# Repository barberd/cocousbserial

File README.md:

# CoCo USB Serial Cartridge

## Description

This board is a cartridge for the Tandy Radio Shack TRS-80 Color Computer (CoCo), an 8 bit computer produced between 1980 and 1991. It provides an interface that allows for a serial connection over a USB connection to a host computer (typically a modern PC).

Schematic is available [here](kicad/6551usb.pdf).

## Source and License

Design maintained at [https://github.com/barberd/cocousbserial](https://github.com/barberd/cocousbserial). [Kicad](https://www.kicad.org/) and [Freerouting](https://github.com/freerouting/freerouting/) were used to design the board.

The design is copyright 2023 by Don Barber. The design is open source, distributed via the GNU GPL version 3 license. Please see the COPYING file for details.

## Interface

The board replicates the interface for original CoCo devices based on the 6551 ACIA chip, such as the Deluxe RS-232 Pak and the Direct Connect Modem Pak. Most of the behavior of the 6551 is duplicated, including the status, command, and control registers. One exception is a lack of hardware loopback support; another is the reset values of the registers (see next paragraph). Interrupts are supported, including those triggered by an empty transmit buffer, received data, or a change in connection status. For the latter, changes in USB connection status are used instead of the DCD and DSR lines used in a rs-232 serial connection.

The registers are not set in the same way as the 6551 upon reset or power-on. As most software does its own initialization of the registers when starting anyway, the lack of this functionality has little practical effect. However, it is possible that the card receiving USB data before the software has set up (or disabled) interrupt handling might lead to an unhandled interrupt, which could potentially lock up the system. The easiest workaround is to just not send data from the USB host until after the CoCo software has initialized the card.

Settings in the command or control registers that do not apply to a USB connection or are performed by the USB protocol (such as baud rate, parity, bitrate, and stop bit settings) are ignored. Bitflags in the status register that do not apply or are abstracted away by the USB module (such as parity, framing, or overrun errors) are tied to 0.

## Why duplicate a legacy hardware interface?

Duplicating the behavior of the 6551 in this way allows one to use original CoCo software written for the Deluxe RS-232 Pak or Direct Connect Modem Pak without modification. Additionally, the use of standard TTL chips (when combined with the USB module) allows one to build the board at home without the need for specialized chips such as a programmed microcontroller.

## USB Capability

The USB module used is the DLP-USB245R. [Here is its manufacturer's page](https://www.dlpdesign.com/usb/usb245r.php). The module can be purchased directly from the manufacturer or from electronics supply houses such as Jameco and Mouser. This module abstracts away much of the heavy lifting needed for USB communications. This module acts as a client device, communicating with a USB host, typically a modern PC. It does NOT support host mode, meaning it can not be used as a host for other peripherals such as keyboard and mice; it only provides a client serial connection. The DLP-USB1232H module is also pin-compatible with the board, though one will need to configure that module into DLP-USB245R (FIFO) mode using the manufacturer's configuration software.

## IO Address

The 6 dip switches (SW1) set the IO addresses for the board. These correspond to address lines A2 through A7. The four addresses used correspond to the board's (and the original 6551 chip's) four registers. Using the switches, one can configure the base address of the board to be any multiple of four within the range of FF00 through FFFC.

The Deluxe RS-232 Pak uses IO addresses FF68-FF6B while the Direct Connect Modem Pak uses FF6C-FF6F. Markings on the board make it straightforward to set the IO address of the board to clone either; this is the easiest way to use the board as one can then leverage existing software.

One may choose to use a different IO address range; this can be helpful if one has multiple paks that would otherwise conflict. If you use a non-standard range, software must be configured, patched, or updated to use the new IO address. Be mindful to review the CoCo's IO mapping and not choose an IO address used by another device, such as a keyboard, joystick, cassette, or disk controller.

## Power Draw

When hooked up to a bench power supply, the card drew 0.2 Amps.

Board version 1.09 added jumper J2 for the source of +5v power for the DLP-USB245R module, either the CoCo or the USB host. The module draws 15mA of power in normal operation. One should choose the USB host if one wants the module recognized by the host as soon as its plugged in, or wants the USB device to remain configured on the host even when the CoCo is power-cycled. One should choose the CoCo if one wants the device recognized only when the CoCo is powered on.

## ROM Socket

A socket for a ROM is also included in the board design. This is entirely optional, as most users today will instead choose to use a third-party communications software package loaded from another source such as disk, SDC, or DriveWire. However, one can add a ROM loaded with the Deluxe RS-232 Cartridge or Direct Connect Modem Cartridge software (or any other cartridge software) if one desires to replicate the original cartridge experience.

The ROM socket is wired for a 27128 EPROM. As the 27128 provides 16k of storage, the board presents this as 2 different banks of 8k each, selected via jumper J1. As such, when writing the EPROM, combine the images with each image aligned to an 8k boundary (eg, at 0 and 8k). If using a ROM IC other than the 27128, one will need to adjust the board design to match the chosen IC. Some other ROM ICs are pin-compatible and will work fine with the existing design.

### Starting the ROM software

Please note that since the cartridge interrupt line is used for serial communications interrupts and not for the cartridge start interrupt, this cartridge does not auto-start. As such, one will need to start the ROM software manually with an "EXEC &HC000" or "EXEC 49152" statement, just as described in the [Deluxe RS-232 Pak](https://colorcomputerarchive.com/repo/Documents/Manuals/Hardware/Deluxe%20RS-232%20Operation%20Manual%20%28Tandy%29.pdf) and [Direct Connect Modem Pak](https://colorcomputerarchive.com/repo/Documents/Manuals/Hardware/Direct%20Connect%20Modem%20Pak%20%28Tandy%29.pdf) manuals.

Note the Color Computer 3 maps the cartridge memory differently than the CoCo 1 and CoCo 2; use "EXEC 57360" or "EXEC &HE010" instead.

## Physical case

The board is sized to fit into an original large CoCo pak, such as the Deluxe RS-232 Pak or a Disk Controller Pak. One can also 3D print a case such as [this  one found on thingiverse](https://www.thingiverse.com/thing:4829413).

## How to order for fabrication

Download 6551usb-fabrication.zip, then upload it to your PCB manufacturer of choice when asked to provide Gerber files. Usually this is found under a 'Quote' option on the website. Search "pcb manufacturing" on any major search engine to get several manufacturers.

Some may have ordered boards and have extra available. Reach out to don &#x40; dgb3.net to explore this.

## Errata

If you have version 1.04 or 1.05 of the board, there a 'bug' in the reset circuit for the change-in-plugged-in-status interrupt in that the interrupt is not cleared when the status register is read. I'm not aware of any software that actually enables this in the first place, so one will likely never encouter the bug. But the fix is simple: bend up pin 6 on U12, and solder it to pin 6 on U5 with a bodge wire. R4 is also no longer needed. This is fixed in 1.06.

Boards prior to versions 1.08 were printed with 10nF capacitors, but .1uf (100nF) capacitors are bit more standard. Either work fine, they're just to smooth out ripples in the power to the ICs.

Board version 1.09 added jumper J2 for the USB module's source of +5v power; see 'Power Draw' section above.

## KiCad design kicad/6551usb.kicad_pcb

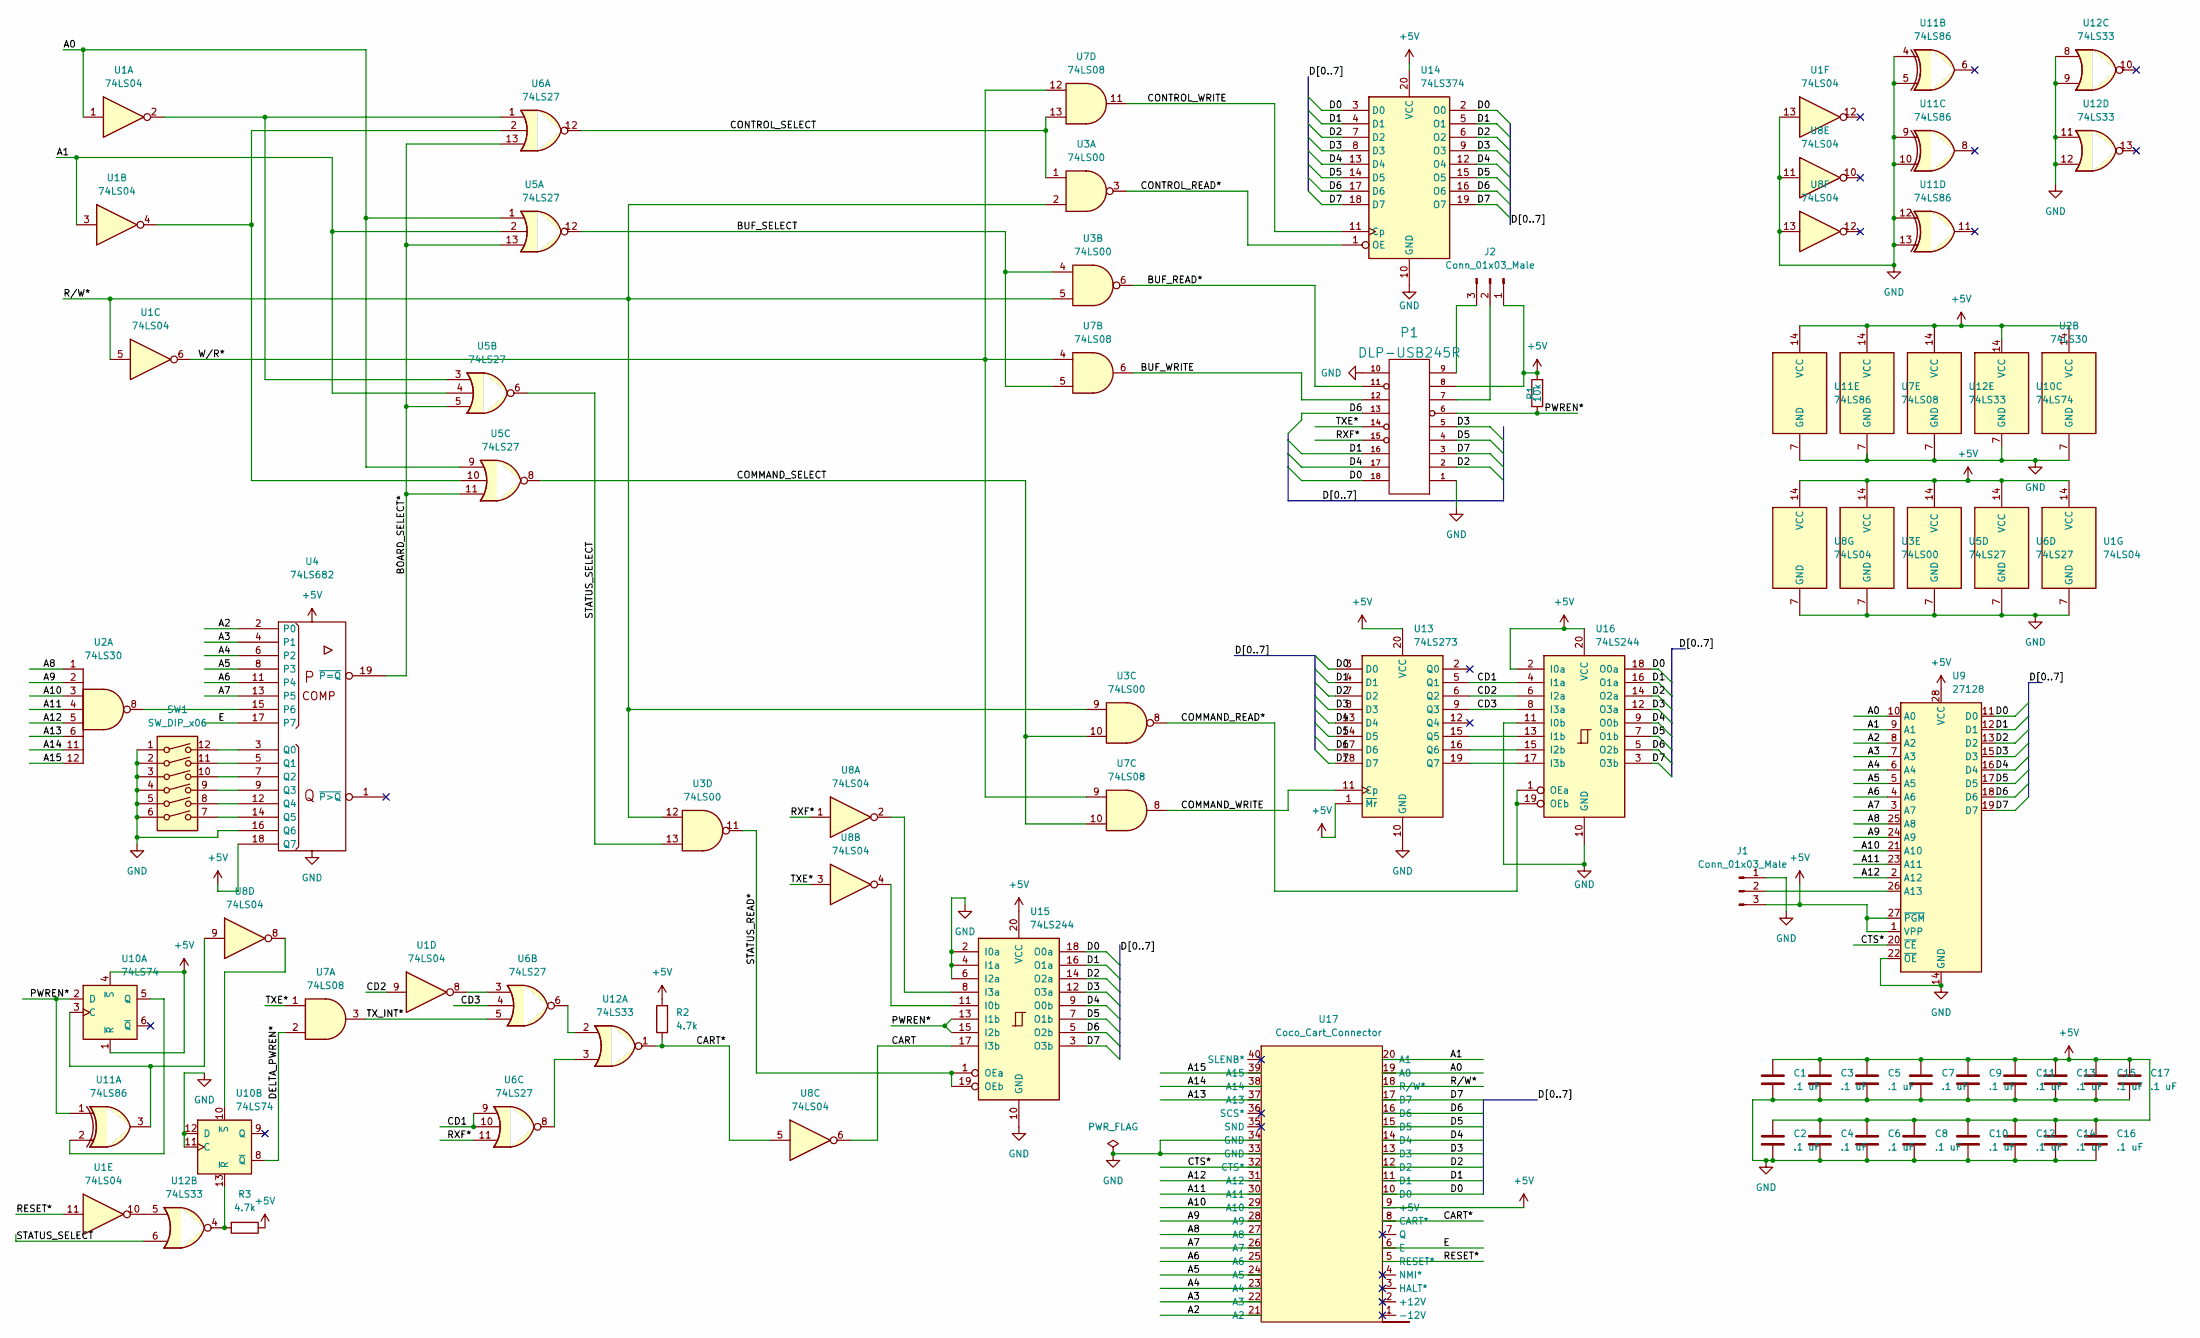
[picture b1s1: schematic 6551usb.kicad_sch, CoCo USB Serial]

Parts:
C1, C2, C3, C4, C5, C6, C7, C8, C9, C10, C11, C12, C13, C14, C15, C16, C17: .1 uF; C_Axial_L3.8mm_D2.6mm_P7.50mm_Horizontal
J1, J2: Conn_01x03_Male; PinHeader_1x03_P2.54mm_Vertical
P1: DLP-USB245R; DIP-18_W7.62mm_Socket
R1: 10k; R_Axial_DIN0207_L6.3mm_D2.5mm_P7.62mm_Horizontal
R2, R3: 4.7k; R_Axial_DIN0207_L6.3mm_D2.5mm_P7.62mm_Horizontal
SW1: SW_DIP_x06; SW_DIP_SPSTx06_Slide_9.78x17.42mm_W7.62mm_P2.54mm
U1, U8: 74LS04; DIP-14_W7.62mm
U2: 74LS30; DIP-14_W7.62mm
U3: 74LS00; DIP-14_W7.62mm
U4: 74LS682; DIP-20_W7.62mm
U5, U6: 74LS27; DIP-14_W7.62mm
U7: 74LS08; DIP-14_W7.62mm
U9: 27128; DIP-28_W15.24mm
U10: 74LS74; DIP-14_W7.62mm
U11: 74LS86; DIP-14_W7.62mm
U12: 74LS33; DIP-14_W7.62mm
U13: 74LS273; DIP-20_W7.62mm
U14: 74LS374; DIP-20_W7.62mm
U15, U16: 74LS244; DIP-20_W7.62mm
U17: Coco_Cart_Connector; Coco_Cart

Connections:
+5V: C1.1, C2.1, C3.1, C4.1, C5.1, C6.1, C7.1, C8.1, C9.1, C10.1, C11.1, C12.1, C13.1, C14.1, C15.1, C16.1, C17.1, J1.3, J2.1, P1.8 (EXTVCC), R1.2, R2.2, R3.1, U1.14 (VCC), U2.14 (VCC), U3.14 (VCC), U4.18 (Q7), U4.20 (Vcc), U5.14 (VCC), U6.14 (VCC), U7.14 (VCC), U8.14 (VCC), U9.1 (VPP), U9.27 (~PGM), U9.28 (VCC), U10.1 (~R), U10.4 (~S), U10.14 (VCC), U11.14 (VCC), U12.14 (VCC), U13.1 (~Mr), U13.20 (VCC), U14.20 (VCC), U15.20 (VCC), U16.2 (I0a), U16.20 (VCC), U17.9 (+5V)
/A0: U1.1, U5.1, U5.9, U9.10 (A0), U17.19 (A0)
/A1: U1.3, U5.2, U5.4, U9.9 (A1), U17.20 (A1)
/A2: U4.2 (P0), U9.8 (A2), U17.21 (A2)
/A3: U4.4 (P1), U9.7 (A3), U17.22 (A3)
/A4: U4.6 (P2), U9.6 (A4), U17.23 (A4)
/A5: U4.8 (P3), U9.5 (A5), U17.24 (A5)
/A6: U4.11 (P4), U9.4 (A6), U17.25 (A6)
/A7: U4.13 (P5), U9.3 (A7), U17.26 (A7)
/A8: U2.1, U9.25 (A8), U17.27 (A8)
/A9: U2.2, U9.24 (A9), U17.28 (A9)
/A10: U2.3, U9.21 (A10), U17.29 (A10)
/A11: U2.4, U9.23 (A11), U17.30 (A11)
/A12: U2.5, U9.2 (A12), U17.31 (A12)
/A13: U2.6, U17.37 (A13)
/A14: U2.11, U17.38 (A14)
/A15: U2.12, U17.39 (A15)
/BOARD_SELECT*: U4.19 (~P=Q), U5.5, U5.11, U5.13, U6.13
/BUF_READ*: P1.11 (RD*), U3.6
/BUF_SELECT: U3.4, U5.12, U7.5
/BUF_WRITE: P1.12 (WR), U7.6
/CART: U8.6, U15.17 (I3b)
/CART*: R2.1, U8.5, U12.1, U17.8 (CART*)
/CD1: U6.9, U6.10, U13.5 (Q1), U16.4 (I1a)
/CD2: U1.9, U13.6 (Q2), U16.6 (I2a)
/CD3: U6.4, U13.9 (Q3), U16.8 (I3a)
/COMMAND_READ*: U3.8, U16.1 (OEa), U16.19 (OEb)
/COMMAND_SELECT: U3.10, U5.8, U7.10
/COMMAND_WRITE: U7.8, U13.11 (Cp)
/CONTROL_READ*: U3.3, U14.1 (OE)
/CONTROL_SELECT: U3.1, U6.12, U7.13
/CONTROL_WRITE: U7.11, U14.11 (Cp)
/CTS*: U9.20 (~CE), U17.32 (CTS*)
/D0: P1.18 (D0), U9.11 (D0), U13.3 (D0), U14.2 (O0), U14.3 (D0), U15.18 (O0a), U16.18 (O0a), U17.10 (D0)
/D1: P1.16 (D1), U9.12 (D1), U13.4 (D1), U14.4 (D1), U14.5 (O1), U15.16 (O1a), U16.16 (O1a), U17.11 (D1)
/D2: P1.2 (D2), U9.13 (D2), U13.7 (D2), U14.6 (O2), U14.7 (D2), U15.14 (O2a), U16.14 (O2a), U17.12 (D2)
/D3: P1.5 (D3), U9.15 (D3), U13.8 (D3), U14.8 (D3), U14.9 (O3), U15.12 (O3a), U16.12 (O3a), U17.13 (D3)
/D4: P1.17 (D4), U9.16 (D4), U13.13 (D4), U14.12 (O4), U14.13 (D4), U15.9 (O0b), U16.9 (O0b), U17.14 (D4)
/D5: P1.4 (D5), U9.17 (D5), U13.14 (D5), U14.14 (D5), U14.15 (O5), U15.7 (O1b), U16.7 (O1b), U17.15 (D5)
/D6: P1.13 (D6), U9.18 (D6), U13.17 (D6), U14.16 (O6), U14.17 (D6), U15.5 (O2b), U16.5 (O2b), U17.16 (D6)
/D7: P1.3 (D7), U9.19 (D7), U13.18 (D7), U14.18 (D7), U14.19 (O7), U15.3 (O3b), U16.3 (O3b), U17.17 (D7)
/DELTA_PWREN*: U7.2, U10.8 (~Q)
/E: U4.17 (P7), U17.6 (E)
/PWREN*: P1.6 (PWREN*), R1.1, U10.2 (D), U11.1, U15.13 (I1b), U15.15 (I2b)
/RESET*: U1.11, U17.5 (RESET*)
/RXF*: P1.15 (RXF*), U6.11, U8.1
/R/W*: U1.5, U3.2, U3.5, U3.9, U3.12, U17.18 (R/W*)
/STATUS_READ*: U3.11, U15.1 (OEa), U15.19 (OEb)
/STATUS_SELECT: U3.13, U5.6, U12.6
/TXE*: P1.14 (TXE*), U7.1, U8.3
/TX_INT*: U6.5, U7.3
/W/R*: U1.6, U7.4, U7.9, U7.12
GND: C1.2, C2.2, C3.2, C4.2, C5.2, C6.2, C7.2, C8.2, C9.2, C10.2, C11.2, C12.2, C13.2, C14.2, C15.2, C16.2, C17.2, J1.1, P1.1 (GND), P1.10 (GND), SW1.1, SW1.2, SW1.3, SW1.4, SW1.5, SW1.6, U1.7 (GND), U1.13, U2.7 (GND), U3.7 (GND), U4.10 (Gnd), U4.16 (Q6), U5.7 (GND), U6.7 (GND), U7.7 (GND), U8.7 (GND), U8.11, U8.13, U9.14 (GND), U9.22 (~OE), U10.7 (GND), U10.11 (C), U10.12 (D), U11.4, U11.5, U11.7 (GND), U11.9, U11.10, U11.12, U11.13, U12.7 (GND), U12.8, U12.9, U12.11, U12.12, U13.10 (GND), U14.10 (GND), U15.2 (I0a), U15.4 (I1a), U15.6 (I2a), U15.10 (GND), U16.10 (GND), U16.11 (I0b), U17.33 (GND), U17.34 (GND)
unnamed: J1.2, U9.26 (A13)
unnamed: J2.2, P1.7 (VCCIO)
unnamed: J2.3, P1.9 (PORTVCC)
unnamed: R3.2, U10.13 (~R), U12.4
unnamed: SW1.7, U4.14 (Q5)
unnamed: SW1.8, U4.12 (Q4)
unnamed: SW1.9, U4.9 (Q3)
unnamed: SW1.10, U4.7 (Q2)
unnamed: SW1.11, U4.5 (Q1)
unnamed: SW1.12, U4.3 (Q0)
unnamed: U1.2, U5.3, U6.1
unnamed: U1.4, U5.10, U6.2
unnamed: U1.8, U6.3
unnamed: U1.10, U12.5
unnamed: U2.8, U4.15 (P6)
unnamed: U8.9, U10.3 (C), U11.3
unnamed: U10.5 (Q), U11.2
unnamed: U8.8, U10.10 (~S)
unnamed: U6.6, U12.2
unnamed: U6.8, U12.3
unnamed: U13.15 (Q5), U16.13 (I1b)
unnamed: U13.16 (Q6), U16.15 (I2b)
unnamed: U13.19 (Q7), U16.17 (I3b)
unnamed: U8.2, U15.8 (I3a)
unnamed: U8.4, U15.11 (I0b)

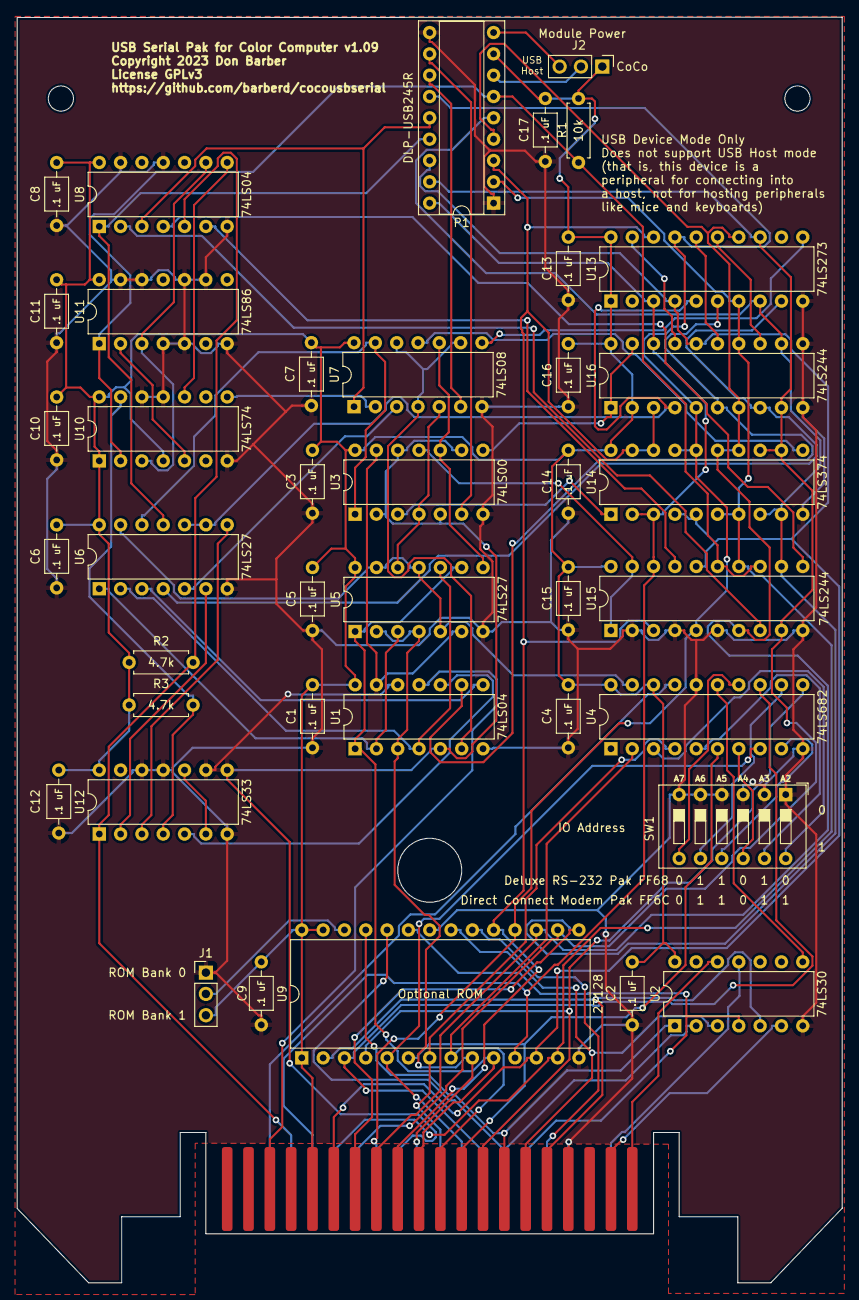
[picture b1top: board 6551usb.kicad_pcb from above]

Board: 2 copper layers, 98.3 x 150.8 mm, 41 parts (0 on the bottom side), 78 nets.

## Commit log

2022-10-20 v1.0
2022-10-20 Updated sheet titles and added screenshot
2022-10-20 Added links
2022-10-20 Fixed language
2022-10-20 Added Coco3 ROM instructions
2022-10-21 Added Bill of Materials
2022-10-21 Added some more details to README
2022-10-28 Updated README with section on register reset values
2022-11-16 Updated image to match 1.01
2022-11-23 Updated to 1.02 to fix E line
2022-11-23 Updated to 1.03 to fix interrupt in status register and extend board to full size
2022-11-23 Fixed BOM
2022-11-25 fixed fab files in kicad folder
2022-11-25 Updated to 1.04 to fix PWREN flipflop set and reset
2022-11-26 Updated for correct logic on PWREN second flipflop
2022-12-03 Added board 'wings' and moved chips around to make board prettier.
2022-12-03 Fixed typo
2022-12-06 Fixed max base IO address
2022-12-13 Add link to schematic
2022-12-14 Add power draw info
2022-12-19 Updated to 1.06
2022-12-24 Updated ears size for 1.07
2023-01-01 v1.08: Updated to .1uf capacitors and slimmed width of card slightly
2023-01-01 Updated readme for 1.08
2023-05-14 Updated to version 1.09 with usb module power jumper
2023-05-14 Updated picture for 1.09
2023-05-14 Clarified README for 1.09
2023-05-14 Fixed J2 label
2023-05-14 Clarified
2023-05-15 Clarified jumper J2

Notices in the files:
kicad/6551usb.kicad_pcb:
Copyright 2023 Don Barber
License GPLv3
